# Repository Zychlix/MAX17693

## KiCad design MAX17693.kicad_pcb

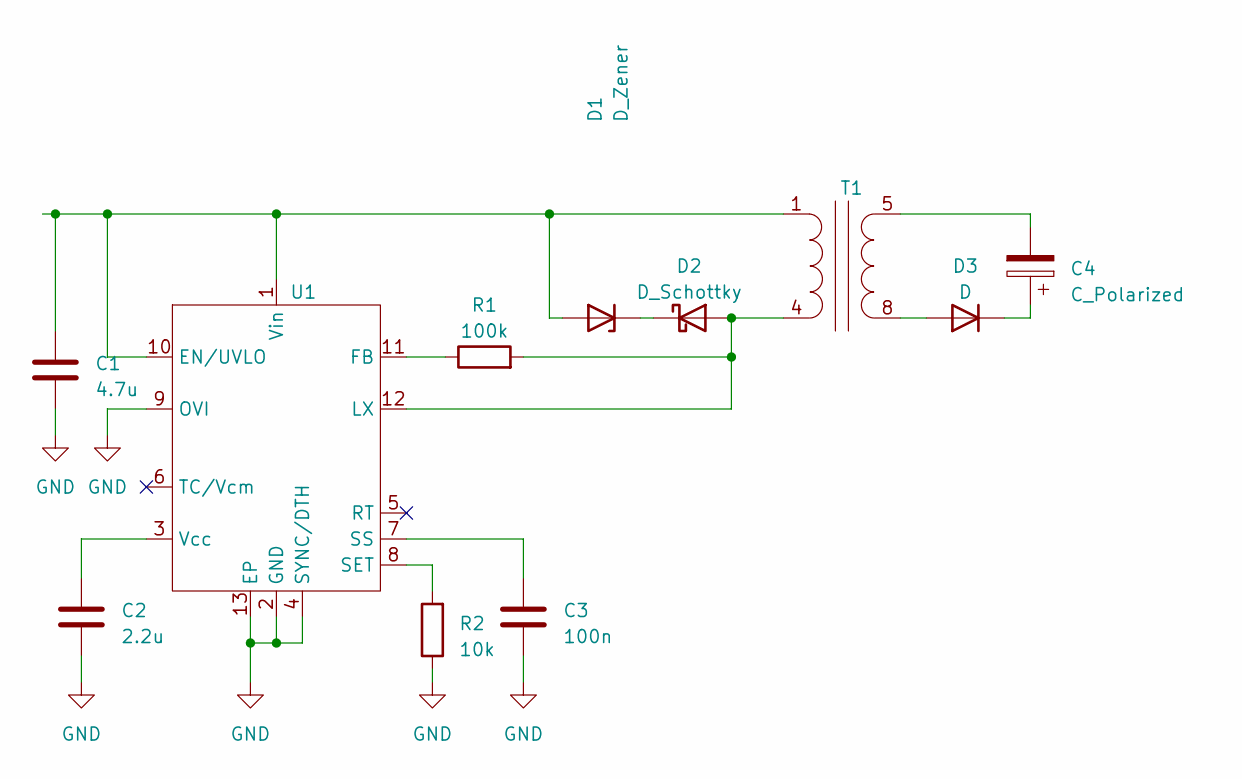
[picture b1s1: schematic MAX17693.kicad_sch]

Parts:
C1: 4.7u; C_0805_2012Metric_Pad1.18x1.45mm_HandSolder
C2: 2.2u; C_0805_2012Metric_Pad1.18x1.45mm_HandSolder
C3: 100n; C_0805_2012Metric_Pad1.18x1.45mm_HandSolder
C4: C_Polarized; CP_Elec_6.3x5.9
D1: D_Zener; D_SMA
D2: D_Schottky; D_SMA
D3: D; D_SMA
R1: 100k; R_0805_2012Metric_Pad1.20x1.40mm_HandSolder
R2: 10k; R_0805_2012Metric_Pad1.20x1.40mm_HandSolder
T1: FA2369-AL
U1: TDFN12L 3x3

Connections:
GND: C1.2, C2.2, C3.2, R2.1, U1.2 (GND), U1.4 (SYNC/DTH), U1.9 (OVI), U1.13 (EP)
unnamed: C4.2, T1.5
unnamed: C1.1, D1.2 (A), T1.1, U1.1 (Vin), U1.10 (EN/UVLO)
unnamed: D1.1 (K), D2.1 (K)
unnamed: D2.2 (A), R1.2, T1.4, U1.12 (LX)
unnamed: D3.2 (A), T1.8
unnamed: C4.1, D3.1 (K)
unnamed: R1.1, U1.11 (FB)
unnamed: R2.2, U1.8 (SET)
unnamed: C3.1, U1.7 (SS)
unnamed: C2.1, U1.3 (Vcc)

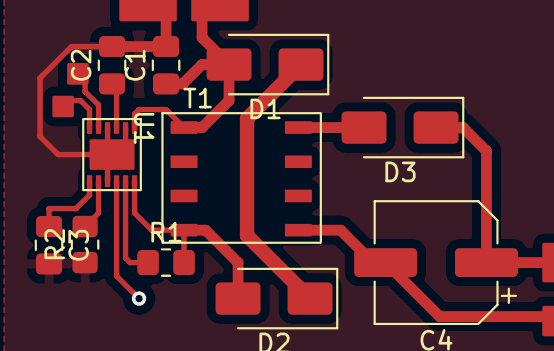
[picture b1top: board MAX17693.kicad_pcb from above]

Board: 2 copper layers, 11 parts (0 on the bottom side), 11 nets.

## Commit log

2023-04-29 initial
